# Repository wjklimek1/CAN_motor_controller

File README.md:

# CAN motor controller
This project is a device that allows control of DC motor by commands on CAN bus. It is based on STM32F103 microcontroller that interprets CAN messages and drives motor using two BTN8982 half-bridges configured as a single H-bridge. 

## Motor driving capabilities
DC motor is controlled with 21kHz PWM signal with 0-100% duty. PWM can be regulated in 0.1% steps - from 0 to 1000. Theoretically max current that MOSFETs can handle is 55A, but it can be futher limited by traces width and connectors. It was tested up to 10A, but should handle much more without any problems. Power supply voltage range is 5-24V.
| Parameter | Min | Max |
|--|--|--|
| voltage | 5V | 24V |
| motor current |  | 55A (10A tested) |

Motor is accelerated slowly by changing PWM duty. If received command orders to immediately set PWM to 100% from 0%, duty is increased slowly in default 10ms intervals. Therefore spinning motor to top speed will take 10s. This property can be disabled by setting "motor inertia" parameter to 0 (see CAN commands table).

## CAN configuration
CAN bus in STM32F103 runs on 250kb/s by default. It can be set to other, hard coded value in the initialization function. Other supported baudrates are 500kb/s and 1Mb/s. 

## Heartbeat
Device emits "heartbeat" frame every 1s. It is an empty frame with ID = 0x444. Heartbeat can be disabled or it's period can be changed in 1s steps up to 255s.

## CAN message structure
Device utilizes two identifiers - 0x444 for commands and 0x445 for requesting data. This values are hard coded too, but can be changed in *canbus.h* file. DLC of CAN messages is not really important, but it cannot be shorter than expected.
In both commands and data requests first byte of message is code of command or data request. In commands next bytes represent values of command parameters. When data request is received by device, it will respond with frame of the same ID and data request code. Next bytes will contain requested data.

## Commands
Following table shows available commands:
|Command | frame ID | DLC | byte 0 (command code) | byte 1 | byte 2 | byte 3 |
|--|--|--|--|--|--|--|
|Set speed | 0x444 | 4 | 1 | rotation direction (0 or 1) | MSB of speed | LSB of speed|
|Set max temperature internal | 0x444 | 2 | 2 | max internal temperature (uint8_t) in Celcius | - | - |
|Set max temperature external | 0x444 | 2 | 3 | max external temperature (uint8_t) in Celcius | - | - |
|Set max current | 0x444 | 4 | 4 | MSB of max current (mA) | LSB of max current (mA) | - |
|Emergency stop | 0x444 | 1 | 5 | - | - | - |
|Set inertia | 0x444 | 2 | 6 | Inertia (ms delay between changing PWM duty) | - | - |
|Set heartbeat | 0x444 | 2 | 7 | heartbeat interval (0 for disabled) | - | - |

## Data requests
To request data, frame of ID = 0x445 and first byte containing data request code can be sent. Device will respond with similar frame, but containing data in next bytes.
 
Following table shows available data requests:
|Data request | frame ID | DLC | byte 0 (data request code) | byte 1 | byte 2 | byte 3 | byte 4 |byte 5 |
|--|--|--|--|--|--|--|--|--|
|Internal temperature | 0x445 | 2 | 1 | Internal temperature (uint8_t) in |Celcius | - | - | - | - |
|External temperature | 0x445 | 2 | 2 | External temperature (uint8_t) in |Celcius | - | - | - | - |
|Power supply voltage | 0x445 | 3 | 3 | MSB of voltage in mV | LSB of voltage in mV | - | - | - |
|Motor current | 0x445 | 3 | 4 | MSB of current in mA | LSB of current in mA | - | - | - |
|Speed | 0x445 | 4 | 5 | rotation direction (0 or 1) | MSB of speed | LSB of speed| - | - |
|Target speed | 0x445 | 4 | 6 | rotation direction (0 or 1) | MSB of speed | LSB of speed| - | - |
|Errors | 0x445 | 5 | 7 | MOSFET fault | overcurrent | overtemperature internal | overtemperature external | emergency stop |

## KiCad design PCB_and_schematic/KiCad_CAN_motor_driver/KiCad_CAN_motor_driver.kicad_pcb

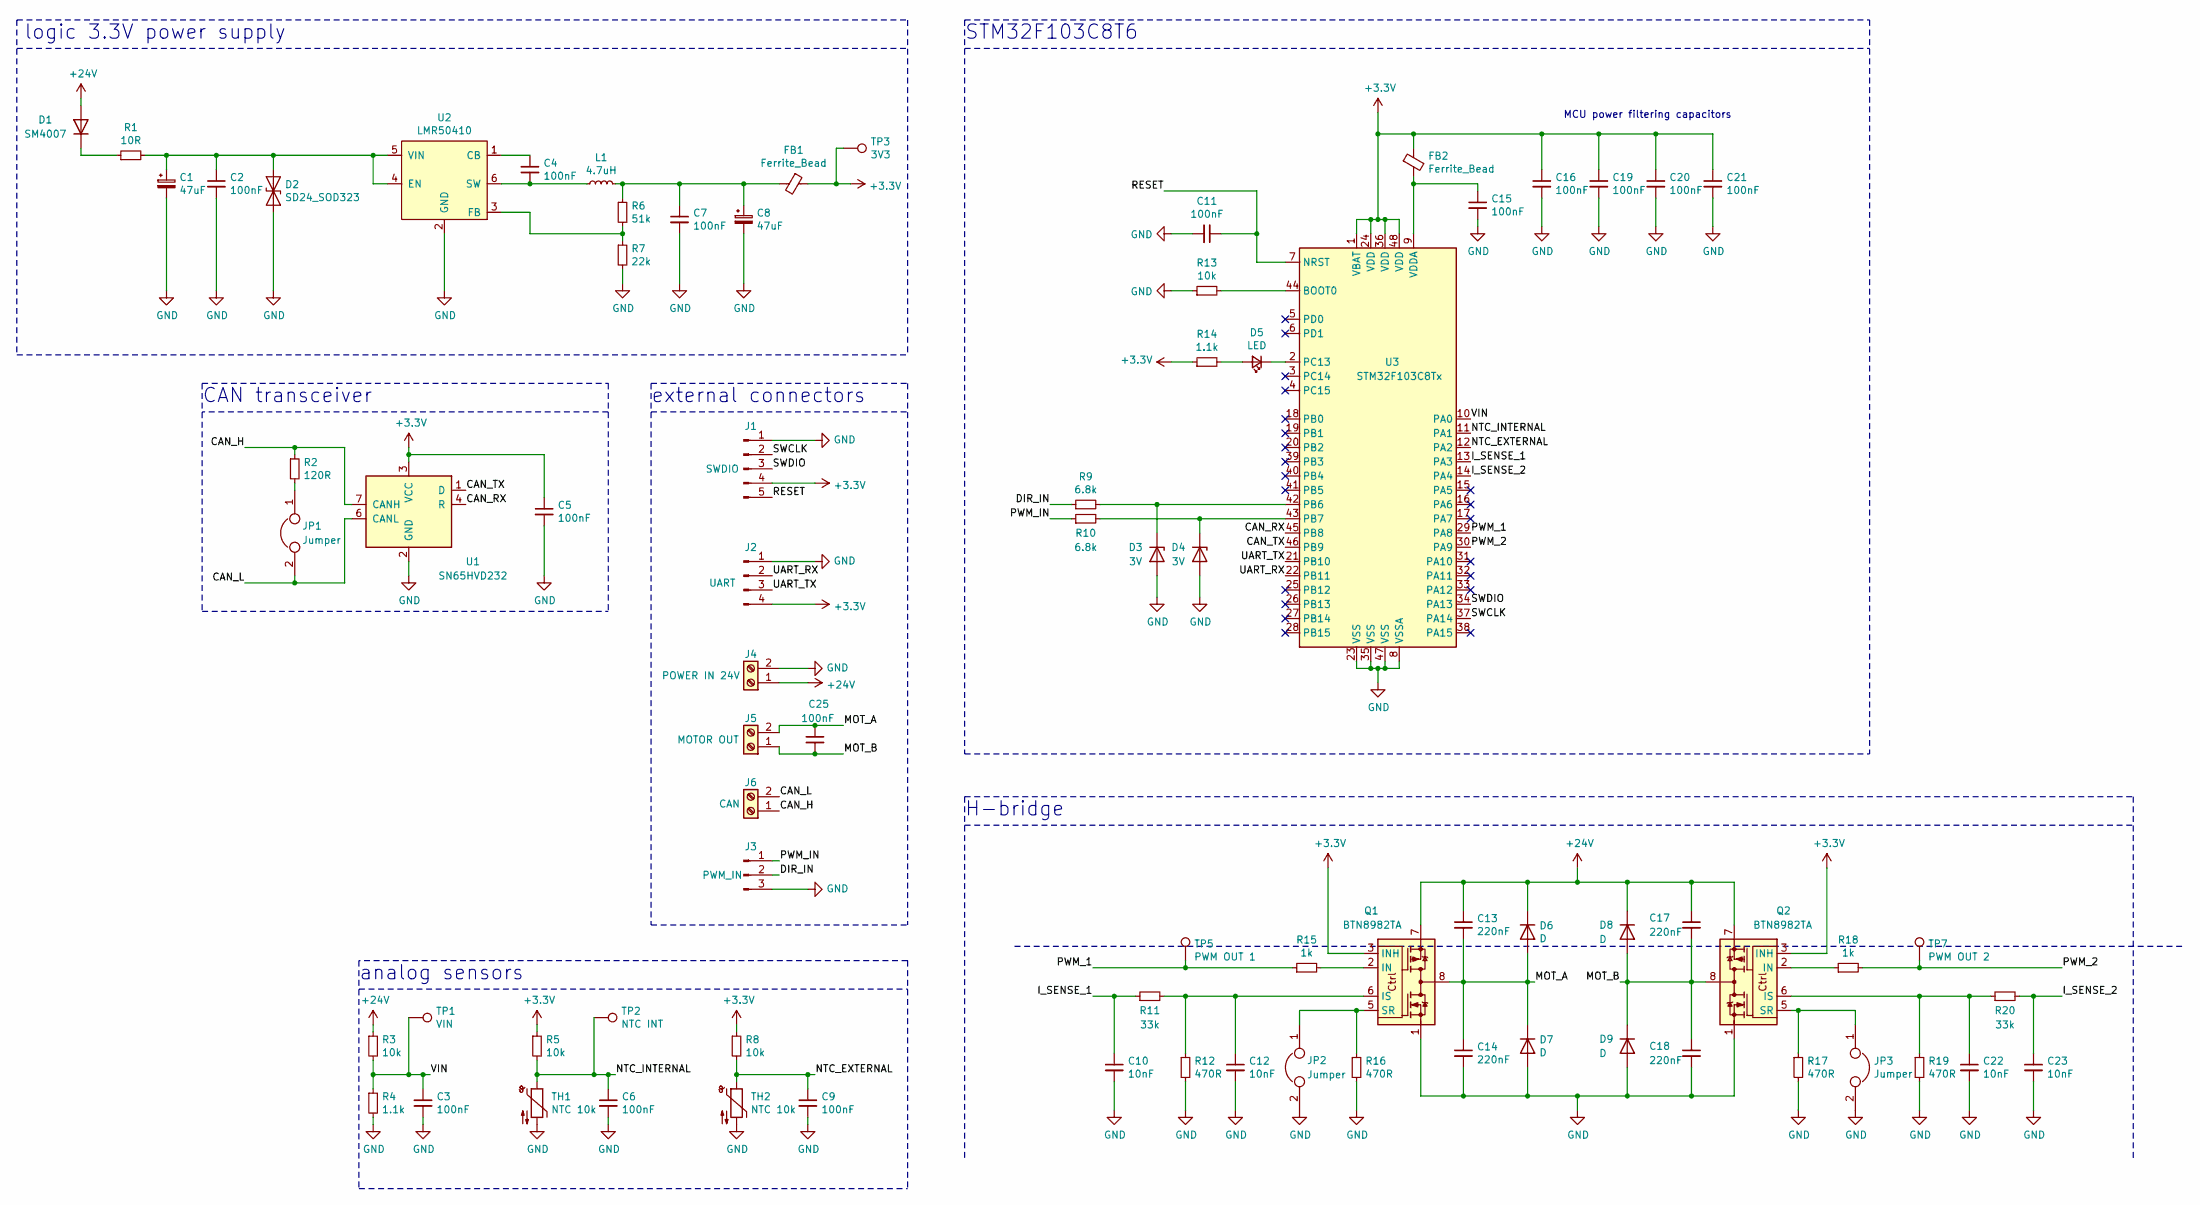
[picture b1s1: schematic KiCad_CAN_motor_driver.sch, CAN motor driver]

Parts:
C1, C8: 47uF; CP_Elec_6.3x5.7
C2, C3, C4, C5, C6, C7, C9, C11, C15, C16, C19, C20, C21: 100nF; C_0805_2012Metric
C10, C12, C22, C23: 10nF; C_0805_2012Metric
C13, C14, C17, C18: 220nF; C_1206_3216Metric_Pad1.33x1.80mm_HandSolder
C25: 100nF; C_1206_3216Metric
D1: SM4007; D_MELF
D2: SD24_SOD323; D_SOD-323
D3, D4: 3V; D_MiniMELF
D5: LED; LED_0805_2012Metric_Castellated
D6, D7, D8, D9: D; D_PowerDI-123
FB1: Ferrite_Bead; L_1206_3216Metric
FB2: Ferrite_Bead; L_1206_3216Metric_Pad1.22x1.90mm_HandSolder
J1: SWDIO; PinHeader_1x05_P2.54mm_Vertical
J2: UART; PinHeader_1x04_P2.54mm_Vertical
J3: PWM_IN; PinHeader_1x03_P2.54mm_Vertical
J4: POWER IN 24V; ScrewTerminal_2_P5.08mm
J5: MOTOR OUT; ScrewTerminal_2_P5.08mm
J6: CAN; ScrewTerminal_2_P5.08mm
JP1: Jumper; SolderJumper-2_P1.3mm_Open_Pad1.0x1.5mm
JP2, JP3: Jumper; SolderJumper-2_P1.3mm_Bridged_Pad1.0x1.5mm
L1: 4.7uH; L_Wuerth_MAPI-4030
Q1, Q2: BTN8982TA; TO-263-7_TabPin8
R1: 10R; R_0805_2012Metric
R2: 120R; R_0805_2012Metric
R3, R5, R8, R13: 10k; R_0805_2012Metric
R4, R14: 1.1k; R_0805_2012Metric
R6: 51k; R_0805_2012Metric
R7: 22k; R_0805_2012Metric
R9, R10: 6.8k; R_0805_2012Metric
R11, R20: 33k; R_0805_2012Metric
R12, R16, R17, R19: 470R; R_0805_2012Metric
R15, R18: 1k; R_0805_2012Metric
TH1: NTC 10k; R_1206_3216Metric_Pad1.30x1.75mm_HandSolder
TH2: NTC 10k; PinHeader_1x02_P2.54mm_Vertical
TP1: VIN; TestPoint_THTPad_D1.0mm_Drill0.5mm
TP2: NTC INT; TestPoint_THTPad_D1.0mm_Drill0.5mm
TP3: 3V3; TestPoint_THTPad_D1.0mm_Drill0.5mm
TP5: PWM OUT 1; TestPoint_THTPad_D1.0mm_Drill0.5mm
TP7: PWM OUT 2; TestPoint_THTPad_D1.0mm_Drill0.5mm
U1: SN65HVD232; SOIC-8_3.9x4.9mm_P1.27mm
U2: LMR50410; SOT-23-6_Handsoldering
U3: STM32F103C8Tx; LQFP-48_7x7mm_P0.5mm

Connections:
+3V3: C5.1, C16.1, C19.1, C20.1, C21.1, FB1.1, FB2.1, J1.4, J2.4, Q1.3 (INH), Q2.3 (INH), R5.1, R8.1, R14.1, TP3.1, U1.3 (VCC), U3.1 (VBAT), U3.24 (VDD), U3.36 (VDD), U3.48 (VDD)
+24V: C13.1, C17.1, D1.2 (A), D6.1 (K), D8.1 (K), J4.1, Q1.7, Q2.7, R3.1
/CAN_H: J6.1, R2.1, U1.7 (CANH)
/CAN_L: J6.2, JP1.2, U1.6 (CANL)
/CAN_RX: U1.4 (R), U3.45 (PB8)
/CAN_TX: U1.1 (D), U3.46 (PB9)
/DIR_IN: J3.2, R9.1
/I_SENSE_1: C10.1, R11.1, U3.13 (PA3)
/I_SENSE_2: C23.1, R20.2, U3.14 (PA4)
/MOT_A: C13.2, C14.1, C25.1, D6.2 (A), D7.1 (K), J5.2, Q1.4, Q1.8
/MOT_B: C17.2, C18.1, C25.2, D8.2 (A), D9.1 (K), J5.1, Q2.4, Q2.8
/NTC_EXTERNAL: C9.1, R8.2, TH2.1, U3.12 (PA2)
/NTC_INTERNAL: C6.1, R5.2, TH1.1, TP2.1, U3.11 (PA1)
/PWM_1: R15.1, TP5.1, U3.29 (PA8)
/PWM_2: R18.2, TP7.1, U3.30 (PA9)
/PWM_IN: J3.1, R10.1
/RESET: C11.1, J1.5, U3.7 (NRST)
/SWCLK: J1.2, U3.37 (PA14)
/SWDIO: J1.3, U3.34 (PA13)
/UART_RX: J2.2, U3.22 (PB11)
/UART_TX: J2.3, U3.21 (PB10)
/VIN: C3.1, R3.2, R4.1, TP1.1, U3.10 (PA0)
GND: C1.2, C2.2, C3.2, C5.2, C6.2, C7.2, C8.2, C9.2, C10.2, C11.2, C12.2, C14.2, C15.2, C16.2, C18.2, C19.2, C20.2, C21.2, C22.2, C23.2, D2.2 (A2), D3.2 (A), D4.2 (A), D7.2 (A), D9.2 (A), J1.1, J2.1, J3.3, J4.2, JP2.2, JP3.2, Q1.1, Q2.1, R4.2, R7.2, R12.2, R13.1, R16.2, R17.2, R19.2, TH1.2, TH2.2, U1.2 (GND), U2.2 (GND), U3.8 (VSSA), U3.23 (VSS), U3.35 (VSS), U3.47 (VSS)
unnamed: C1.1, C2.1, D2.1 (A1), R1.2, U2.4 (EN), U2.5 (VIN)
unnamed: C4.1, U2.1 (CB)
unnamed: C4.2, L1.1, U2.6 (SW)
unnamed: C7.1, C8.1, FB1.2, L1.2, R6.1
unnamed: C12.1, Q1.6 (IS), R11.2, R12.1
unnamed: C15.1, FB2.2, U3.9 (VDDA)
unnamed: C22.1, Q2.6 (IS), R19.1, R20.1
unnamed: D1.1 (K), R1.1
unnamed: D3.1 (K), R9.2, U3.42 (PB6)
unnamed: D4.1 (K), R10.2, U3.43 (PB7)
unnamed: D5.1 (K), U3.2 (PC13)
unnamed: D5.2 (A), R14.2
unnamed: JP1.1, R2.2
unnamed: JP2.1, Q1.5 (SR), R16.1
unnamed: JP3.1, Q2.5 (SR), R17.1
unnamed: Q1.2 (IN), R15.2
unnamed: Q2.2 (IN), R18.1
unnamed: R6.2, R7.1, U2.3 (FB)
unnamed: R13.2, U3.44 (BOOT0)

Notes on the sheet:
logic 3.3V power supply
MCU power filtering capacitors
external connectors
CAN transceiver
analog sensors
H-bridge
STM32F103C8T6

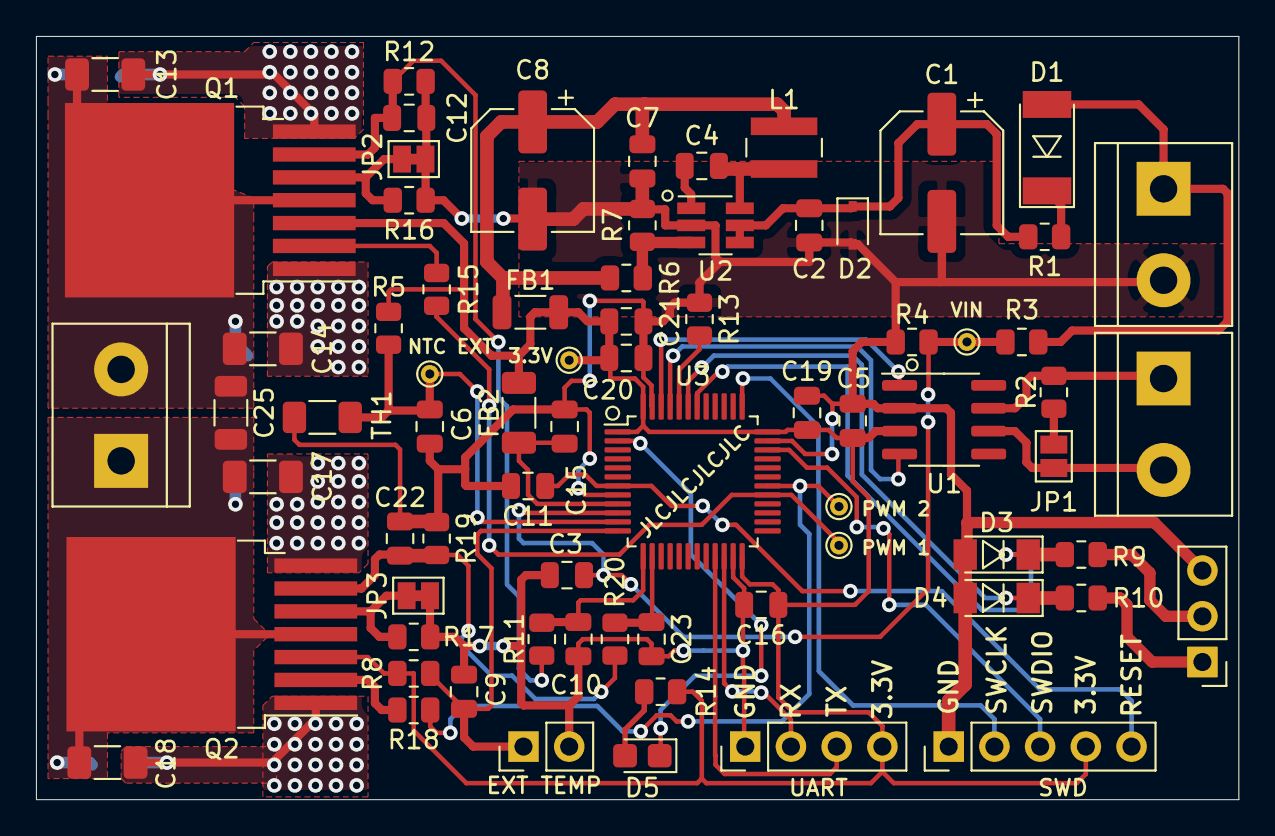
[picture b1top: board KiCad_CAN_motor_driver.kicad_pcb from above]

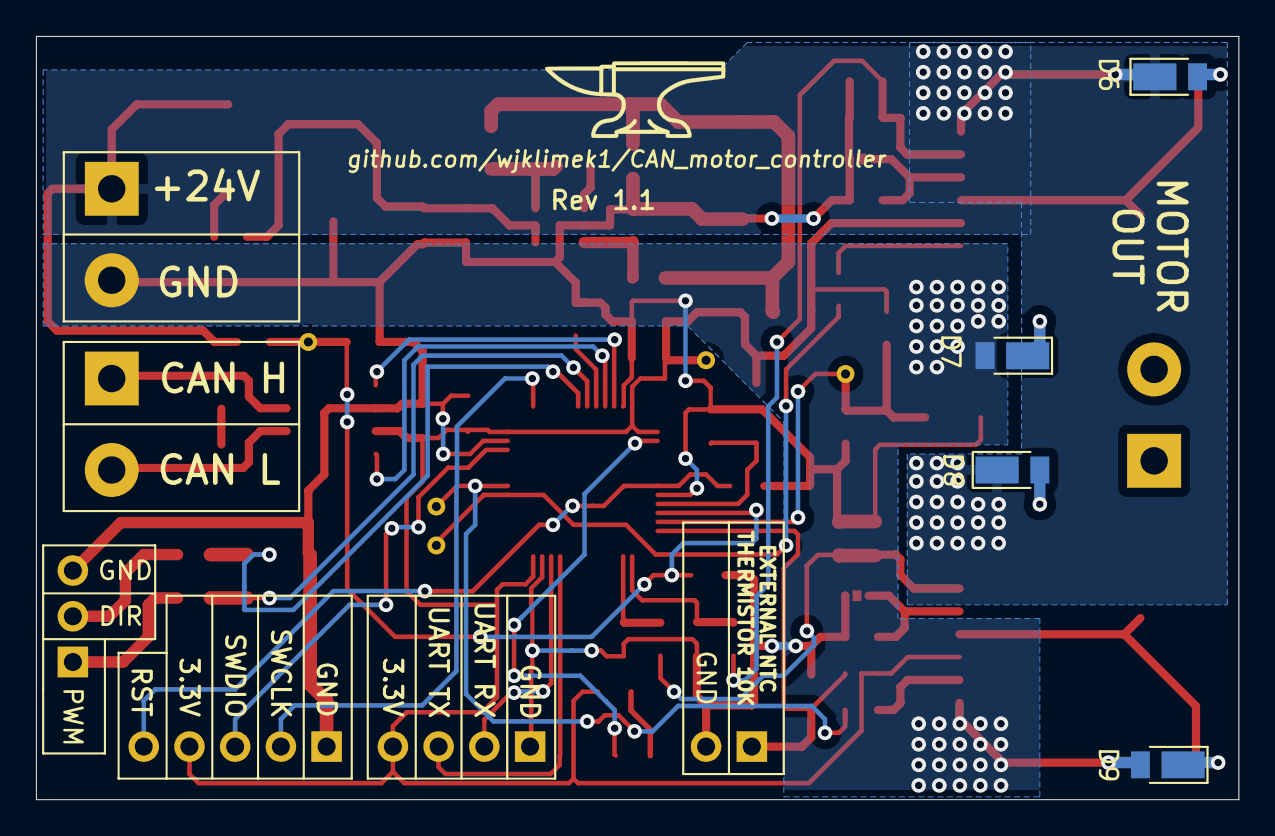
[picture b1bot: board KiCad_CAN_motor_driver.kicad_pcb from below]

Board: 2 copper layers, 66.8 x 42.4 mm, 77 parts (4 on the bottom side), 42 nets.

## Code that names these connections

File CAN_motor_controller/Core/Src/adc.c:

#include <stdint.h>
#include "stm32f103xb.h"

#include "adc.h"
#include "timers.h"

void ADC_init(void)
{
  //init ADC GPIOs - PA0, PA1, PA2, PA3, PA4
  RCC->APB2ENR |= RCC_APB2ENR_AFIOEN;                                                                  //enable alternate function clock
  RCC->APB2ENR |= RCC_APB2ENR_IOPAEN;                                                                  //enable GPIOA clock
  GPIOA->CRL &= ~(GPIO_CRL_MODE0 | GPIO_CRL_MODE1 | GPIO_CRL_MODE2 | GPIO_CRL_MODE3 | GPIO_CRL_MODE4); //set GPIOs to analog mode
  GPIOA->CRL &= ~(GPIO_CRL_CNF0 | GPIO_CRL_CNF1 | GPIO_CRL_CNF2 | GPIO_CRL_CNF4 | GPIO_CRL_CNF4);      //set GPIOs as inputs

  //configure ADC clock source
  RCC->CFGR &= ~RCC_CFGR_ADCPRE;       //clear ADC clock prescaler bits
  RCC->CFGR |= RCC_CFGR_ADCPRE_DIV8;   //set ADC prescaler to 8 to get 8HMz ADC clock
  RCC->APB2ENR |= RCC_APB2ENR_ADC1EN;  //enable ADC clock
  //init ADC1
  ADC1->CR2 |= ADC_CR2_ADON;           //wake up ADC form power-down mode
  delay_ms(1);                         //wait some time between power-up and calibration
  ADC1->CR2 |= ADC_CR2_CAL;            //start ADC calibration
  while(ADC1->CR2 & ADC_CR2_CAL)
    {
    };  //wait until calibration is completed

  ADC1->CR2 |= (ADC_CR2_CONT | ADC_CR2_DMA | ADC_CR2_EXTSEL);  //enable continuous mode, enable DMA, set software as conversion trigger
  ADC1->CR1 |= ADC_CR1_SCAN;                                   //enable scan mode
  ADC1->CR2 |= ADC_CR2_TSVREFE;                                //enable internal temperature sensor
  ADC1->CR2 |= ADC_CR2_EXTTRIG;                                //enable conversion on external trigger

  ADC1->SQR1 = 0; //reset register
  ADC1->SQR1 |= ((6 - 1) << ADC_SQR1_L_Pos);  //set number of conversions to 6
  ADC1->SQR3 |= (0 << ADC_SQR3_SQ1_Pos);      //PA0 as 1st conversion
  ADC1->SQR3 |= (1 << ADC_SQR3_SQ2_Pos);      //PA1 as 2nd conversion
  ADC1->SQR3 |= (2 << ADC_SQR3_SQ3_Pos);      //PA2 as 3rd conversion
  ADC1->SQR3 |= (3 << ADC_SQR3_SQ4_Pos);      //PA3 as 4th conversion
  ADC1->SQR3 |= (4 << ADC_SQR3_SQ5_Pos);      //PA4 as 5th conversion
  ADC1->SQR3 |= (16 << ADC_SQR3_SQ6_Pos);     //TempSensor as 6th conversion

  //set sampling time of all conversions to 239.5 cycles for best stability
  ADC1->SMPR2 |= ADC_SMPR2_SMP0;
  ADC1->SMPR2 |= ADC_SMPR2_SMP1;
  ADC1->SMPR2 |= ADC_SMPR2_SMP2;
  ADC1->SMPR2 |= ADC_SMPR2_SMP3;
  ADC1->SMPR2 |= ADC_SMPR2_SMP4;
  ADC1->SMPR1 |= ADC_SMPR1_SMP16;
}

void ADC_start_with_DMA(uint16_t *results_array)
{
  // DMA initialization and start
  RCC->AHBENR |= RCC_AHBENR_DMA1EN;               //enable DMA1 clock
  DMA1_Channel1->CCR &= ~(DMA_CCR_EN);            //disable DMA channel associated with ADC1
  DMA1_Channel1->CPAR = (uint32_t) &ADC1->DR;     //set peripherial address to read from ADC's data register
  DMA1_Channel1->CMAR = (uint32_t) results_array; //set memory address to write to
  DMA1_Channel1->CNDTR = 6;                       //set number of data transmissions
  DMA1_Channel1->CCR |= DMA_CCR_CIRC;             //enable circular mode
  DMA1_Channel1->CCR |= DMA_CCR_MSIZE_0;          //set memory data size to 16bit word
  DMA1_Channel1->CCR |= DMA_CCR_PSIZE_0;          //set peripherial data size to 16bit word
  DMA1_Channel1->CCR |= DMA_CCR_MINC;             //enable memory address incrementation
  DMA1_Channel1->CCR &= ~(DMA_CCR_PL);            //clear DMA channel priority bits to set lowest priority
  DMA1_Channel1->CCR |= DMA_CCR_EN;               //enable DMA1 channel 1

  // start ADC conversions
  ADC1->CR2 |= ADC_CR2_ADON;    //final ADC power up
  ADC1->CR2 |= ADC_CR2_SWSTART; //ADC start
}

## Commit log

2021-03-20 Initial PCB version
    + initial schematic
    + initial PCB design
2021-03-21 Power traces optimization
    +power traces optimized for lower resistance
2021-03-21 Added 3D models of PCB in .step and .stl formats
2021-03-22 PDF schematic
    + schematic in PDF format for quick preview
    + changed resistors on PWM inputs from 1K to 6.8K to decrease Zener diodes current
    + little tweaks in PCB traces
2021-03-22 Added vias on power traces near input, added testpoints
2021-03-22 Added JLC PCB ID placeholder,
    +traces optimization
2021-03-23 Final PCB version (rev 1.0)
    + reduced amount of vias
    + increased distance between vias
    + removed vias from half-bridge's bottom and moved them closer to motor output pads
    + changed PWM input connector to goldpin
    + added jumper (default open) connecting terminating resistor to CAN bus
    + updated PDF schematic
2021-04-04 First version of STM32 code (PWM, PLL)
    Initial version of code for STM32F103C8T6
    + function to switch MCU clock source from HSI to 64MHz PLL
    + function to init timer 1 with 2 PWM outputs on pins PA8 and PA9
2021-04-05 ADC + DMA
    + reading analog values from PA0, PA1, PA2, PA3 and internal temperature sensor
    + working ADC+DMA for continous readings without CPU utilization
    + moved clock configuration and timers functions to separate files
2021-04-05 Create .gitattributes
    + added gitattributes to fix GitHub's mislabeled language problem
2021-04-05 Update .gitattributes
    + fixed gitattibutes
2021-04-08 UART with printf() support
    + added UART3 initialization and data send functions
    + added printf() implementation suitable for embedded systems
    + standardized code formatting
2021-04-08 Simple CANbus frame transmission
    + CANbus initialization
    + Transmission of single CAN frame using mailbox0
2021-04-11 Receiving CAN bus messages
    + standarized CAN bus frame structure for transmission and reception
    + functions to check if there are any pending messages in mailboxes
    + function to receive CAN bus message from mailboxes
2021-04-12 Enabled CAN1 reception interrupts
    + CAN1 reception IRQs enabled and ready to be implemented
2021-04-12 Interrupt based CAN reception with ring buffer
    + implemented CAN RX interrupts
    + implemented simple ring buffer to keep incoming CAN messages
    + changed CANbus_msg_t from struct to typedef struct
    + removed file accidendtaly placed in "Startup" folder
2021-04-22 Thermistor and getTick()
    + added function to convert thermistor resistance to temperature
    + added function getTick() returning current value of milliseconds counter
2021-04-22 Enabled CAN ID filters
    + enabled CAN ID filters to allow only commands and data requests IDs
    + fixed bug in function releasing mailbox1
2021-04-26 Utilizing all TX mailboxes, fixed volatile warning
    + utilizing all 3 TX mailboxes for CAN
    + change return data for CAN1_transmit_message() function
    + fixed "discards volatile quantifier" warnings
2021-04-26 DMA initialization placed in ADC code, unified UART3_init() with actual core clock
    + DMA initialization placed in ADC code
    + unified UART3_init() with actual core clock
    + Doxygen style comments in ringbuffer files
2021-04-28 Command interpreter
    + enabled automatic CAN retransmission
    + function interpreting commands received from CAN
2021-04-29 Enabled automatic bus-off recovery
    + enabled automatic bus off recovery
2021-04-29 Commands setting internal parameters
    + commands for setting global variables: target motor speed, max current, max internal temperature, max external temperature
    + doxygen style commands in canbus.c file
2021-04-30 Changing motor speed with interpolation
    + function triggered in regular intervals that will interpolate motor speed
    + fixed bug in thermistor calculations
2021-04-30 Fixed motor speed interpolation
    + fixed bugs in motor speed interpolation
    +fixed potential zero-division error in temperature reading
    + fixed wrong calculation of input voltage
    + request for current motor speed now returns also direction
    +
2021-05-01 curent calculation
    + calculation of motor current
2021-05-01 Emergency stop, heartbeat, motor inertia
    + settable motor inertia
    + emergency stop command - stops motor without interpolation
    + function transmitting heartbeat
2021-05-01 Fixed freezing after emergency stop
    + after emergency stop all motor related variables are set to 0
2021-05-01 Heartbeat interval and reading errors
    + added function reading following errors: overcurrent, overtemperature internal and external, emergency stop, mosfet fault
    + heartbeat can be enabled or disabled
    + settable heartbeat interval 1-255 seconds
2021-05-17 PCB and schematic rev 1.1
    + revision 1.1 of schematic and PCB
2021-05-17 README - commands decription
2021-06-12 Added back-emf diodes, fixed reading errors
2021-09-04 Separate function for CAN filter config
    + Separate function to configure CAN filters. Gives more flexibility in filter configuration.
    + fixed some spelling errors and misplaced line in schematic
2021-09-04 Completed comments for thermistor.c and uart.c
